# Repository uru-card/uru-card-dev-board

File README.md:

# uru-card-dev-board
PCB design for simple development board for URU Card project

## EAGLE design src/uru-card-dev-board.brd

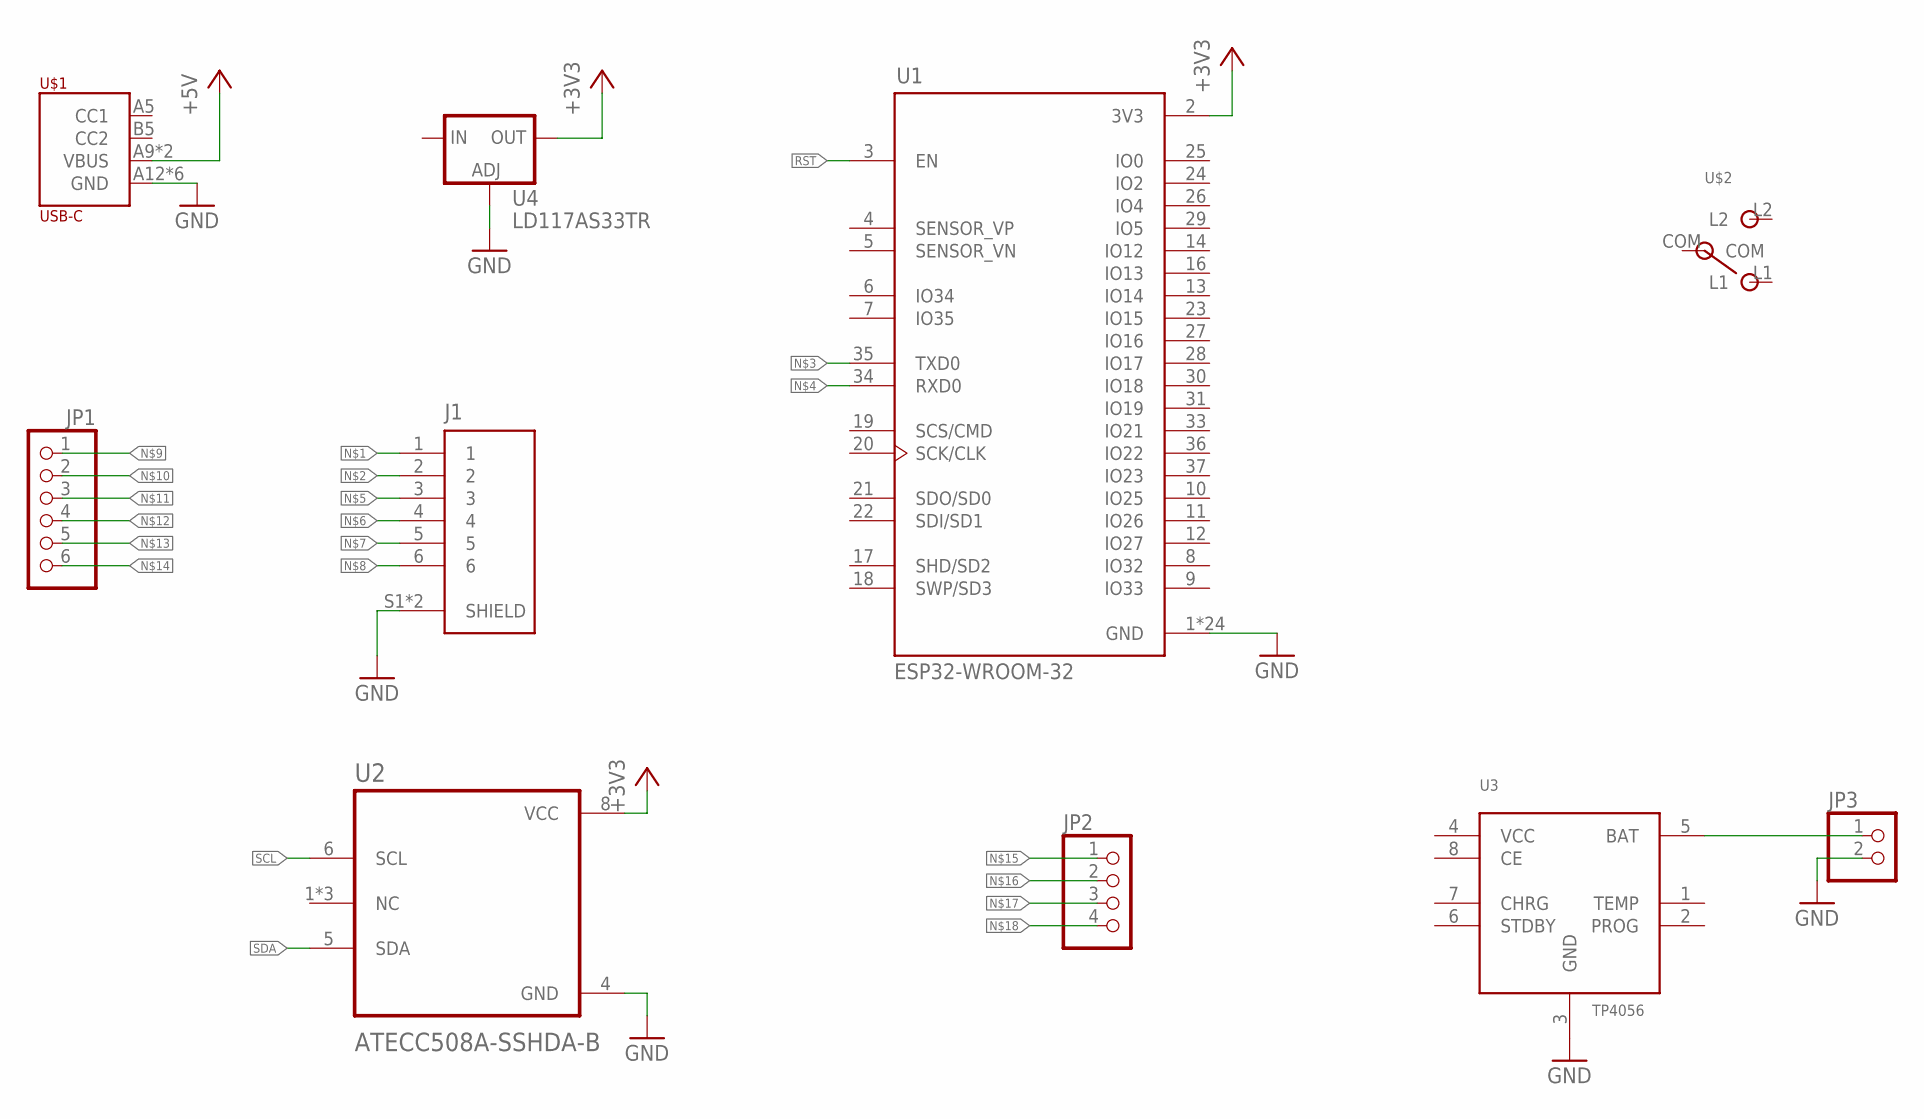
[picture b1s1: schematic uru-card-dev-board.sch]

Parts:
J1: SM06B-GHS-TB(LF)(SN); JST_SM06B-GHS-TB(LF)(SN)
JP1: PINHD-1X6/90; 1X06/90
JP2: PINHD-1X4; 1X04
JP3: PINHD-1X2; 1X02
U1: ESP32-WROOM-32; MODULE_ESP32-WROOM-32
U2: ATECC508A-SSHDA-B; SOIC127P600X175-8N
U3: TP4056; SOP-8
U4: LD117AS33TR; SOT223
U$1: USB-C
U$2: MSK-12C02_SMD_SPDT_SWITCH; MSK-12C02

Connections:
+3V3: U1.2 (3V3), U2.8 (VCC), U4.4 (OUT)
+5V: U$1.A9 (VBUS), U$1.B9 (VBUS)
GND: J1.S1 (SHIELD), J1.S2 (SHIELD), JP3.2, U1.1 (GND), U1.15 (GND), U1.38 (GND), U1.39_1 (GND), U1.39_2 (GND), U1.39_3 (GND), U1.39_4 (GND), U1.39_5 (GND), U1.39_6 (GND), U1.39_7 (GND), U1.39_8 (GND), U1.39_9 (GND), U1.39_10 (GND), U1.39_11 (GND), U1.39_12 (GND), U1.39_13 (GND), U1.39_14 (GND), U1.39_15 (GND), U1.39_16 (GND), U1.39_17 (GND), U1.39_18 (GND), U1.39_19 (GND), U1.39_20 (GND), U1.39_21 (GND), U2.4 (GND), U3.3 (GND), U4.1 (ADJ), U$1.A12 (GND), U$1.B12 (GND), U$1.P$7 (GND), U$1.P$8 (GND), U$1.P$9 (GND), U$1.P$10 (GND)
unnamed: JP3.1, U3.5 (BAT)
RST: U1.3 (EN)
SCL: U2.6 (SCL)
SDA: U2.5 (SDA)

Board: 2 copper layers, 10 parts (7 on the bottom side), 4 nets, no tracks yet.

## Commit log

2020-10-24 Added schematics
